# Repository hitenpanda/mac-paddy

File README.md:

# mac-paddy
A 6 key macro-pad with an EC11 Rotary Encoder that is able to control all of the devices sharing my home network. This will make my life a bit easier.

## Parts List:

### BOM -

1\. MCU - XIAO ESP32-S3 **Buy Link: https://robocraze.com/products/seeed-studio-xiao-esp32-s3-development-board-supports-wi-fi-bluetooth-5-0?variant=47775391645920&country=IN&currency=INR&utm_medium=product_sync&utm_source=google&utm_content=sag_organic&utm_campaign=sag_organic Documentation: https://www.seeedstudio.com/Seeed-Studio-XIAO-ESP32C6-p-5884.html** ~ $9.30

2\. Switches - Akko V5 Creamy Blue Pro Switch **Buy Link: https://stackskb.com/store/akko-v5-creamy-blue-pro-switch-pack-of-45/** ~ $12.66

3\. Encoder - EC11 Rotary Encoder **Buy Link: https://www.sunrom.com/p/rotary-encoder-ec11-flat-d-shaft-20mm** ~ $0.59

4\. LEDs - WS2812B LEDs **Buy Link: https://sharvielectronics.com/product/ws2812b-mini-rgb-smd-led-3535-led-type-package/** ~ $1.79

5\. Diodes - 1N4148 Fast Switching Diodes **Buy Link: https://hubtronics.in/1002?search=1n4148** ~ $3.74

6\. Screen - 0.91" OLED Display **Buy Link: https://robu.in/product/0-91-inch-128x32-i2c-iic-serial-blue-oled-lcd-display-module/** ~ $2.23

7\. Solder Wire - Noel Solder Wire **Buy Link: https://robu.in/product/solder-wire-1-00mm-50gm/** ~ $3.16

8\. Flux - Solder Flux **Buy Link: https://www.amazon.in/Electron-Soldering-Syringe-No-Clean-Electronics/dp/B0GTMJHBJ4?source=ps-sl-shoppingads-lpcontext&psc=1&smid=A3C7Z4RVM9A3G1** ~ $4.21

9\. Multimeter - **Buy Link: https://www.amazon.in/Themisto-TH-M98-Digital-Multimeter-Counts/dp/B097RS212G?source=ps-sl-shoppingads-lpcontext&smid=A2K5VGK3OPN02U&th=1** ~ $8.42

10\. Cutter - Wire Cutter **Buy Link: https://www.amazon.in/Electronic-Spices-Nipper-07-Aluminium-Stripper/dp/B0BLNX18FM?source=ps-sl-shoppingads-lpcontext&psc=1&smid=AJ6SIZC8YQDZX** ~ $1.48

11\. Solder helper - **Buy Link: https://www.amazon.in/Serplex%C2%AE-Soldering-Flexible-Insulated-Alligator/dp/B0DFQ6G523?source=ps-sl-shoppingads-lpcontext&smid=A3T8K809Q96RB6&th=1** ~ $9.29

# Total - $56.87 **excluding PCBs and 3D print.**
# Approx Total **including PCBs and 3D print.** - $75 to $80 *with shipping included*.

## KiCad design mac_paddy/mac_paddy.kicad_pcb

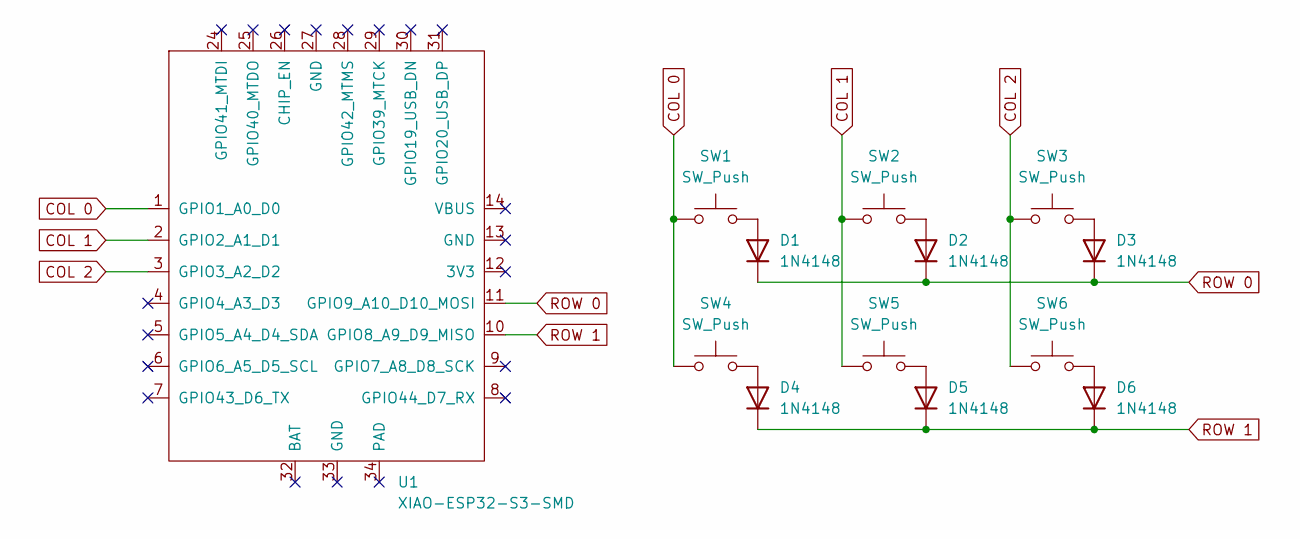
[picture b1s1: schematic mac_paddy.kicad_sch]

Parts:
D1, D2, D3, D4, D5, D6: 1N4148; Diode_DO-35
SW1, SW2, SW3, SW4, SW5, SW6: SW_Push; MX_PCB_1.00u
U1: XIAO-ESP32-S3-SMD

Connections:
COL 0: SW1.1, SW4.1, U1.1 (GPIO1_A0_D0)
COL 1: SW2.1, SW5.1, U1.2 (GPIO2_A1_D1)
COL 2: SW3.1, SW6.1, U1.3 (GPIO3_A2_D2)
unnamed: D1.2 (A), SW1.2
unnamed: D2.2 (A), SW2.2
unnamed: D3.2 (A), SW3.2
unnamed: D4.2 (A), SW4.2
unnamed: D5.2 (A), SW5.2
unnamed: D6.2 (A), SW6.2
ROW 0: D1.1 (K), D2.1 (K), D3.1 (K), U1.11 (GPIO9_A10_D10_MOSI)
ROW 1: D4.1 (K), D5.1 (K), D6.1 (K), U1.10 (GPIO8_A9_D9_MISO)

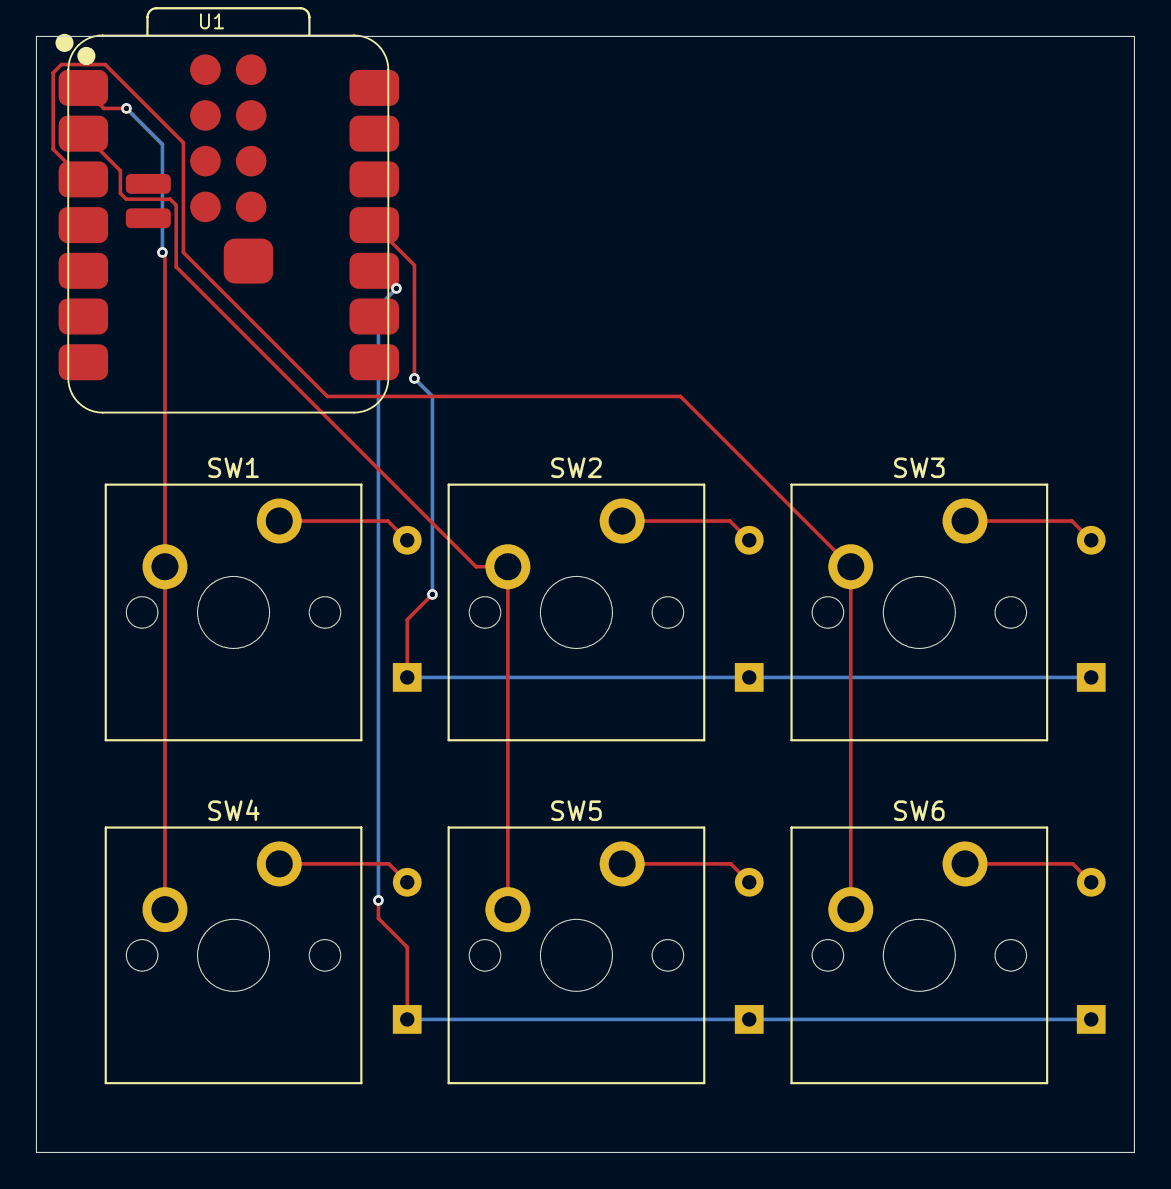
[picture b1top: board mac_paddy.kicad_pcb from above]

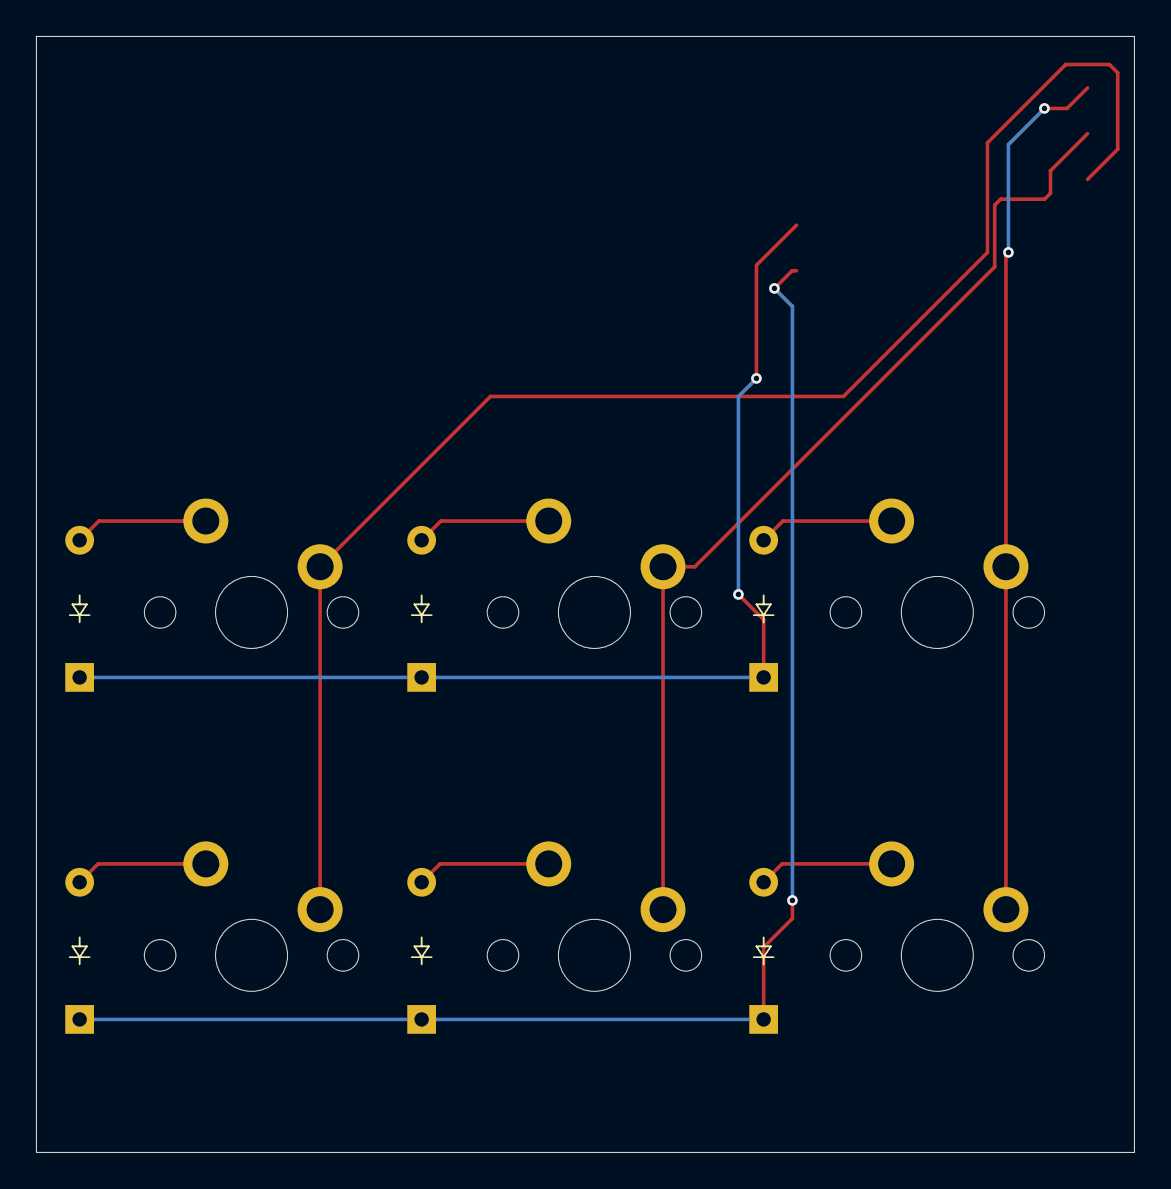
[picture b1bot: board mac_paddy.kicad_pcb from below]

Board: 2 copper layers, 61.0 x 62.0 mm, 13 parts (6 on the bottom side), 11 nets.

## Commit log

2026-06-19 Started PCB design.
2026-06-19 Corrected MCU info.
2026-06-20 PCB design and export completed!
2026-06-22 Exported the final PCB and designed an enclosure for it.
2026-06-24 Made the knob for the EC11 and exported 3 files for the 3D print.
2026-06-30 FInally completed the firmware.
2026-06-30 Made the BOM and updated Readme.
